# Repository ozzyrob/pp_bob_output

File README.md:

# pp_bob_output
 Beagleboneblack modular cnc cape system Output Board
 
To be used with pp_cape, converts 5v logic to 3v3 logic
  * Provides 8 Ouputs for Step direction (can be used for pru direct out)
  * Provides 5 Inputs ESTOP & Home\Limit switches
  * Provides 4 Outputs for relays, indicators or whatever.

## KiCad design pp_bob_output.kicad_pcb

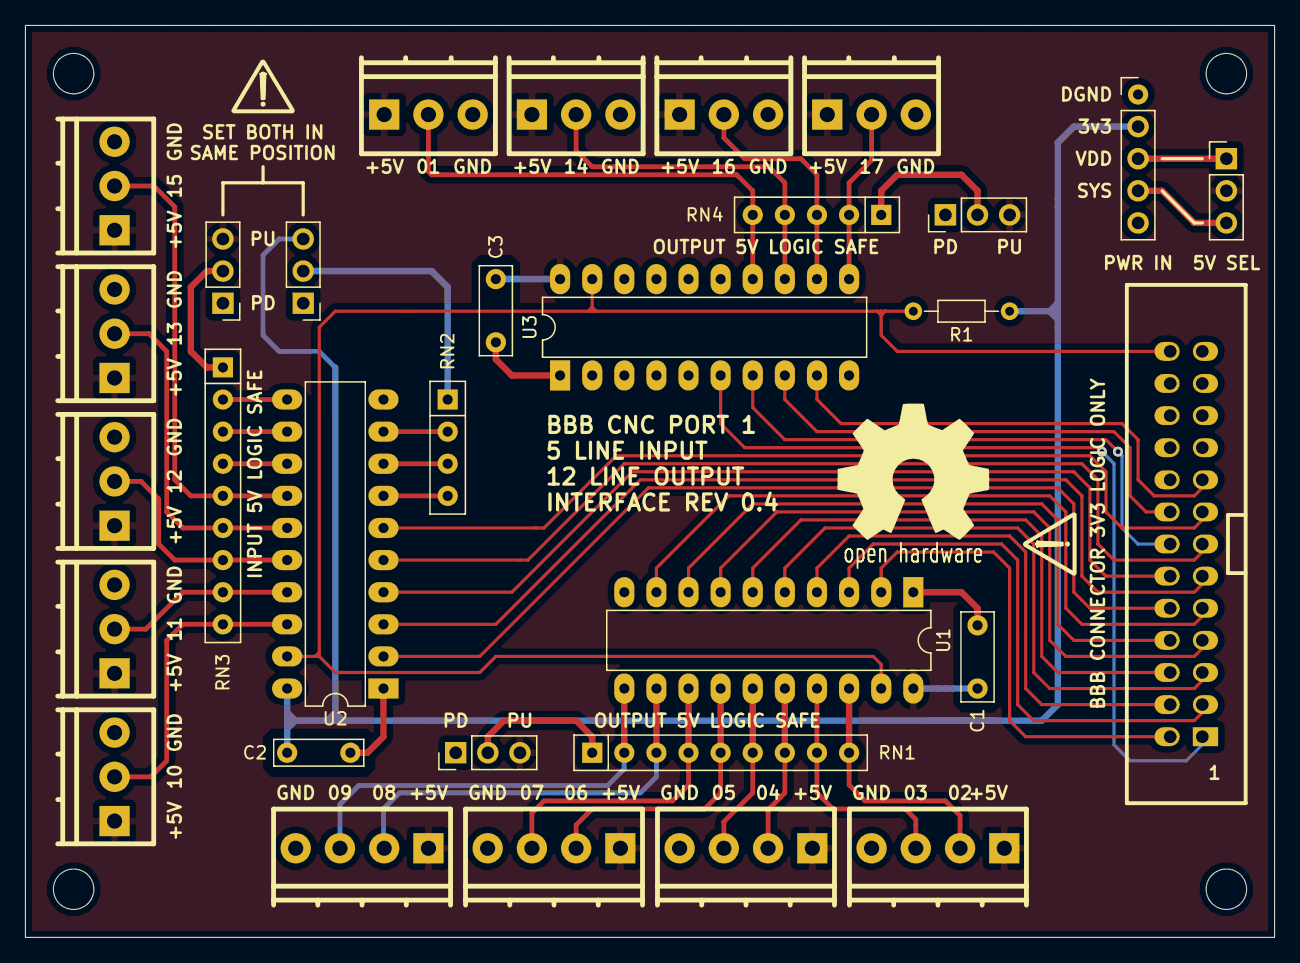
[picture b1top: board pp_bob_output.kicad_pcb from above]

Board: 2 copper layers, 98.8 x 72.1 mm, 31 parts (0 on the bottom side), 50 nets.

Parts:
C1, C3: 100n; C_Rect_L7.0mm_W2.5mm_P5.00mm
C2: 100n; C_Rect_L7.0mm_W2.0mm_P5.00mm
J_IN_1, J_IN_2, J_IN_3, J_IN_4, J_IN_5: ST_1x03; pt_1,5-3-3,5-h
J_OUT_1, J_OUT_2, J_OUT_3, J_OUT_4: ST_1x04; pt_1,5-4-3,5-h
J_OUT_5, J_OUT_6, J_OUT_7, J_OUT_8: ST_1x03; pt_1,5-3-3,5-h
P4: 13X2; vasch_strip_13x2
PWRIN_1: 1X5; Pin_Header_Straight_1x05_Pitch2.54mm
PWRSEL_1: 1X3; Pin_Header_Straight_1x03_Pitch2.54mm
R1: 4K7; R_Axial_DIN0204_L3.6mm_D1.6mm_P7.62mm_Horizontal
RN1, RN3: 4k7; R_Array_SIP9
RN2: 3k3; R_Array_SIP4
RN4: 4k7; R_Array_SIP5
SEL_1, SEL_2, SEL_3, SEL_4: 1X3; Pin_Header_Straight_1x03_Pitch2.54mm
U1: 74LS540; DIP-20_W7.62mm_LongPads
U2: 74LVC245; DIP-20_W7.62mm_LongPads
U3: 74LS541; DIP-20_W7.62mm_LongPads

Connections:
+3V3: C2.1, PWRIN_1.2, R1.1, SEL_2.3, U2.20
+5V: C1.1, C3.1, J_IN_1.1, J_IN_2.1, J_IN_3.1, J_IN_4.1, J_IN_5.1, J_OUT_1.1, J_OUT_2.1, J_OUT_3.1, J_OUT_4.1, J_OUT_5.1, J_OUT_6.1, J_OUT_7.1, J_OUT_8.1, PWRSEL_1.2, SEL_1.3, SEL_3.3, SEL_4.3, U1.20, U3.20
/IN-10: J_IN_1.2, RN3.9, U2.18
/IN-11: J_IN_2.2, RN3.8, U2.17
/IN-12: J_IN_3.2, RN3.7, U2.16
/IN-13: J_IN_4.2, RN3.6, U2.15
/IN-15: J_IN_5.2, RN3.5, U2.14
/OUT-01: J_OUT_5.2, RN4.5, U3.14
/OUT-02: J_OUT_1.2, RN1.9, U1.18
/OUT-03: J_OUT_1.3, RN1.8, U1.17
/OUT-04: J_OUT_2.2, RN1.7, U1.16
/OUT-05: J_OUT_2.3, RN1.6, U1.15
/OUT-06: J_OUT_3.2, RN1.5, U1.14
/OUT-07: J_OUT_3.3, RN1.4, U1.13
/OUT-08: J_OUT_4.2, RN1.3, U1.12
/OUT-09: J_OUT_4.3, RN1.2, U1.11
/OUT-14: J_OUT_6.2, RN4.4, U3.13
/OUT-16: J_OUT_7.2, RN4.3, U3.12
/OUT-17: J_OUT_8.2, RN4.2, U3.11
/SYS_+5v: PWRIN_1.3, PWRSEL_1.1
/VDD_+5v: PWRIN_1.4, PWRSEL_1.3
CHIP_ENABLE: P4.26, R1.2, U1.19, U2.19, U3.19
DB_01: P4.1, U3.6
DB_02: P4.2, U1.2
DB_03: P4.3, U1.3
DB_04: P4.4, U1.4
DB_05: P4.5, U1.5
DB_06: P4.6, U1.6
DB_07: P4.7, U1.7
DB_08: P4.8, U1.8
DB_09: P4.9, U1.9
DB_10: P4.10, U2.2
DB_11: P4.11, U2.3
DB_12: P4.12, U2.4
DB_13: P4.13, U2.5
DB_14: P4.14, U3.7
DB_15: P4.15, U2.6
DB_16: P4.16, U3.8
DB_17: P4.17, U3.9
GND: C1.2, C2.2, C3.2, J_IN_1.3, J_IN_2.3, J_IN_3.3, J_IN_4.3, J_IN_5.3, J_OUT_1.4, J_OUT_2.4, J_OUT_3.4, J_OUT_4.4, J_OUT_5.3, J_OUT_6.3, J_OUT_7.3, J_OUT_8.3, P4.18, P4.19, P4.20, P4.21, P4.22, P4.23, P4.24, P4.25, PWRIN_1.1, SEL_1.1, SEL_2.1, SEL_3.1, SEL_4.1, U1.1, U1.10, U2.1, U2.10, U3.1, U3.2, U3.3, U3.4, U3.5, U3.10
unnamed: RN1.1, SEL_1.2
unnamed: RN2.1, SEL_2.2
unnamed: RN2.2, U2.9
unnamed: RN2.3, U2.8
unnamed: RN2.4, U2.7
unnamed: RN3.1, SEL_3.2
unnamed: RN3.2, U2.11
unnamed: RN3.3, U2.12
unnamed: RN3.4, U2.13
unnamed: RN4.1, SEL_4.2

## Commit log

2017-04-14 Inital Commit
2017-04-14 Initial V0.2 commit
2017-04-14 Initial V0.3 commit
2017-04-14 Clean up in line with pp_bob_output_v0.3
2017-04-14 Clean up in line with pp_bob_intput_v0.3
2017-04-16 Rotated Pu-Pd headers for U2 & U3 cleaned up silkscreen
2017-04-17 Cleaned up schematic
2017-04-23 Modified schematic for seperate termianls, PCB modded with terminals spaced equally. Tracks to be rerouted
2017-04-23 Fixed silkscreen & and other details, good for manu
2017-04-24 Adjust position of PWR IN & 5V SEL headers
2017-04-24 Move 26 pin connector to allow for box type
2017-04-25 Finalised for production, gerbers created, good to go
2017-04-25 Invoice & gerber zip file added.
2017-07-17 Add preproduction jpeg
2017-07-17 Add new file
2017-09-20 Replace pp_bob_output-NPTH.TXT
2017-09-20 Replace pp_bob_output.GBL
2017-09-20 Replace pp_bob_output.GBO
2017-09-20 Replace pp_bob_output.GBS
2017-09-20 Replace pp_bob_output.GML
2017-09-20 Replace pp_bob_output.GTL
2017-09-20 Replace pp_bob_output.GTO
2017-09-20 Replace pp_bob_output.GTS
2017-09-20 Upload New File
2017-09-20 Fix silkscreen to top
2017-09-20 Add docs
2017-09-20 Add .gitattribute
